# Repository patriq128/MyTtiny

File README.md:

# MyTtiny

My own development board based on the **ATtiny3217** microcontroller.

## Features

One of the main reasons I made this board was for my own projects. However, I also wanted to make it useful enough for other people to use.

- **Compact size**

  I tried to make this board as small as possible, and I think I did a pretty good job. The board measures only **29.718 × 17.018 mm**.

- **USB-C**

  The board uses a USB-C connector, making it easy to power, program, and communicate with. I also included the required configuration resistors, so **USB-C to USB-C cables work properly**.

- **UART**

  I decided to add a **CH340N** USB-to-UART converter. This allows the board to communicate with a computer through USB and makes it possible to upload programs and use a serial monitor.

- **NeoPixel LED**

  I wanted the board to provide visual feedback without requiring any external hardware, so I added a programmable RGB LED.

- **Labeled Pins**

  Every header pin is labeled on both the top and bottom sides of the PCB, making it easier to identify the pins regardless of which side of the board you are looking at.

## Hardware

  ### Microcontroller

  For this board, I decided to use the **ATtiny3217**. It is small, power-efficient, and capable enough for a wide range of simple embedded projects.

  ### USB Interface

  The board uses a USB-C connector. I chose USB-C because it is compact, modern, and convenient to use.

  I also added a USB protection chip to help protect the USB data lines from electrical faults.

  The USB interface is connected to a **CH340N** USB-to-UART converter, which provides serial communication between the computer and the ATtiny3217.

  ### Power

  There are two voltage levels available on the board:

  - **5V** — Supplied by the USB-C connector or the 5V pin header. It is regulated down to 3.3V using an **AP2112K** voltage regulator.
  - **3.3V** — This is the main operating voltage of the board.

  I also added a small red LED to indicate when the board is powered.

  ### NeoPixel LED

  The board includes an **SK6812MINI** programmable RGB LED. It can be controlled by the ATtiny3217 and used to display different colors or provide visual feedback.

  ### Button

  There is also a small user button that can be used for any purpose in your code.

## Programming

  ### Bootloader

  Before uploading your first program, you need to install a bootloader on the ATtiny3217.

  The bootloader can be uploaded using the **three UPDI pins** located at the bottom of the board.

  For this project, I am using the bootloader provided by **[MegaTinyCore](https://github.com/SpenceKonde/megaTinyCore)**.

  ### Uploading Programs

  Once the bootloader is installed, you can upload programs and use the serial monitor through the USB-C port connected to the **CH340N** USB-to-UART converter.

## Pinout

The name of every pin is printed on both the top and bottom sides of the PCB.

> **Note:** On the top side, the pins are labeled without the **"P"** prefix.

### Official Pinout Image

## Board

  ### Schematic

  I tried to make the schematic as clean and easy to understand as possible.

  ### PCB

  #### Top

  #### Bottom

## Production

The main goal of this project is to have the board manufactured. I plan to have it manufactured by **JLCPCB**, which will manufacture the PCBs and assemble the components for me.

In the [`production`](production/) folder, you can find:

- **Gerber files**
- **Pick-and-place file**
- **BOM file**

## Why I Made This

Honestly, I originally made this board because I was bored.

I also didn't really want to use some of the existing development boards available to me, so I decided to design my own.

I chose the **ATtiny3217** as the main microcontroller because I wanted to try something different instead of using more common chips such as the RP2040 or ESP32.

In the end, it became a small development board that I can use for my own projects while also making the design available for anyone else who might find it useful.

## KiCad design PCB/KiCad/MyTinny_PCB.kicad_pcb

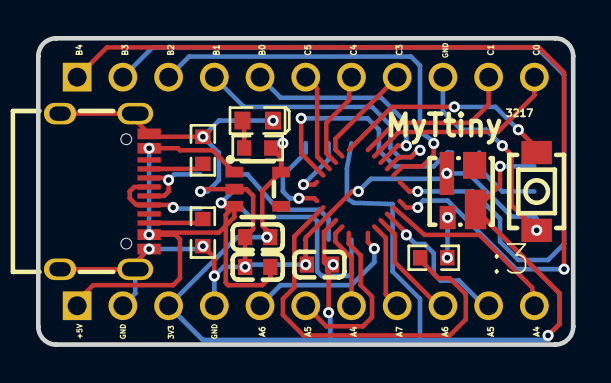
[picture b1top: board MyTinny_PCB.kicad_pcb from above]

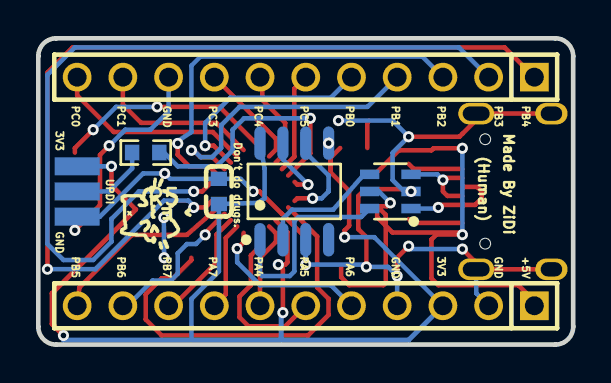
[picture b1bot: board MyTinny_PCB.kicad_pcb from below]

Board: 2 copper layers, 29.7 x 17.0 mm, 19 parts (7 on the bottom side), 12 nets.

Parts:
C1, C3, C4: 1uF; C0603
C2: 100nF; C0603
D1: USBLC6-2SC6_C5250994; SOT-23-6_L2.9-W1.6-P0.95-LS2.8-BL
H1, H2: 2011-1X11G00SB; HDR-TH_11P-P2.54_2011-1X11G00SB
LED1: LED-0603_R; LED0603_RED
R1, R2: 5.1kΩ; R0603
R3: 2.2kΩ; R0603
R4: 330Ω; R0603
R5: 1kΩ; R0603
SW1: HX 3X4X2-2P-1.6N TACTILE SWITCH; KEY-SMD_L4.0-W3.0-LS4.9-1
U1: SK6112MINI-RG; LED-SMD_4P-L3.7-W3.5-SK6812SMINI-001
U2: CH340N_C2977777; SOP-8_L4.9-W3.9-P1.27-LS6.0-BL
U3: AP2112K-3.3TRG1(MS); SOT-23-5_L2.9-W1.6-P0.95-LS2.7-BR
U5: edge_conn_pad3; PADPAD4X1.5 3PAD_SIGNALS
USBC1: TYPE-C-31-M-12; USB-C_SMD-TYPE-C-31-M-12_1

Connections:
+5V: C3.2, D1.5, H1.1, U3.1, U3.3, USBC1.A4B9, USBC1.B4A9
D+: D1.6, U2.1
D-: D1.4, U2.2
GND: C1.1, C2.2, C3.1, C4.1, D1.2, H1.2, H1.4, H2.9, LED1.2, R1.1, R2.1, SW1.1, U1.4, U2.3, U3.2, U5.3, USBC1.1, USBC1.2, USBC1.3, USBC1.4, USBC1.A1B12, USBC1.B1A12
R1_2: R1.2, USBC1.A5
R2_2: R2.2, USBC1.B5
R3_2: LED1.1, R3.2
R4_1: R4.1, U1.1
U5_2: R5.2, U5.2
USBC1_A6: D1.1, USBC1.A6, USBC1.B6
USBC1_B7: D1.3, USBC1.A7, USBC1.B7
VCC: C1.2, C2.1, C4.2, H1.3, R3.1, U1.2, U2.5, U2.8, U3.5, U5.1
